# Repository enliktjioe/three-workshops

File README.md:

# three-workshops
HfK Bremen - Three Workshops course from Ralf Baecker

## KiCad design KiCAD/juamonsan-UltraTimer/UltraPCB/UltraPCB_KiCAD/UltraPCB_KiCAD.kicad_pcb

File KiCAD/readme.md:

# KiCAD Notes

## Day 3 - Designing, Simulating and Running Installation with [Processing.org](http://processing.org/)

## Day 2 - KiCAD PCB continuation

Using reference:
https://github.com/juamonsan/UltraTimer

A custom PCB board with a STM32 microcontroller, 7 seg display, a buzzer and many leds... In the shape of the #1 hero of all galaxy. Made with [KiCAD](https://www.kicad.org/), [Inkscape](https://inkscape.org/), [Gingerbread](https://github.com/wntrblm/Gingerbread) and [Stretch](https://github.com/JarrettR/Stretch). Programmed with [STM32CubeIDE](https://www.st.com/en/development-tools/stm32cubeide.html).

## Day 1 - KiCAD introduction

15.07.2025

Prof. Ralf Baecker

https://github.com/rlfbckr/workshops/tree/main

Presentation:
https://docs.google.com/presentation/d/1FQOJmnPphsIvtIlYlx94JYpmJ64v6YoRFoZGHLRAc9c/edit?slide=id.gb1fd486fc7_0_359#slide=id.gb1fd486fc7_0_359

Miro Canvas:
https://miro.com/app/board/uXjVJfeq8kw=/

Getting Started:
https://docs.kicad.org/6.0/en/getting_started_in_kicad/getting_started_in_kicad.html#basic_concepts_and_workflow

Example projects:

- https://www.martinhesselmeier.com/saroskop/
- https://gieskes.nl/

Other References:

- https://github.com/joanbono/awesome-kicad

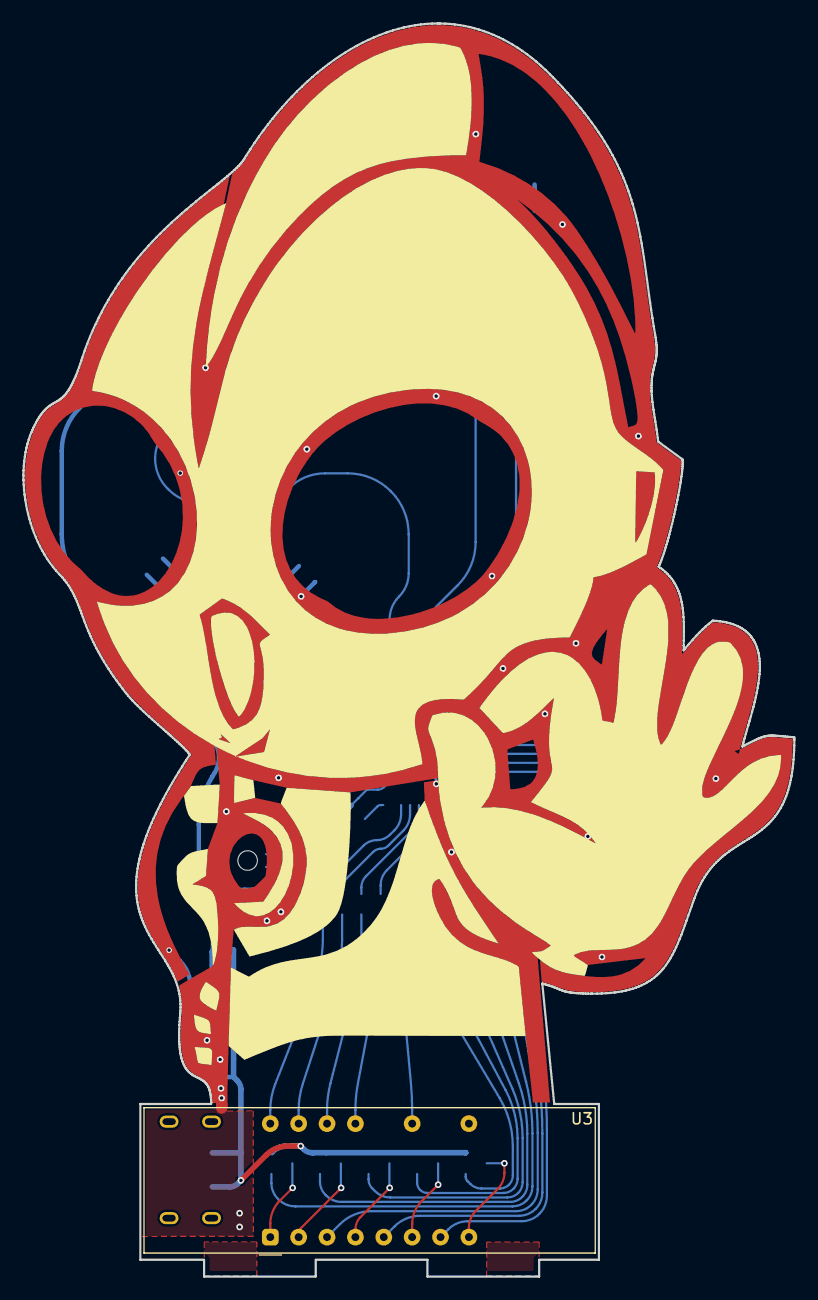
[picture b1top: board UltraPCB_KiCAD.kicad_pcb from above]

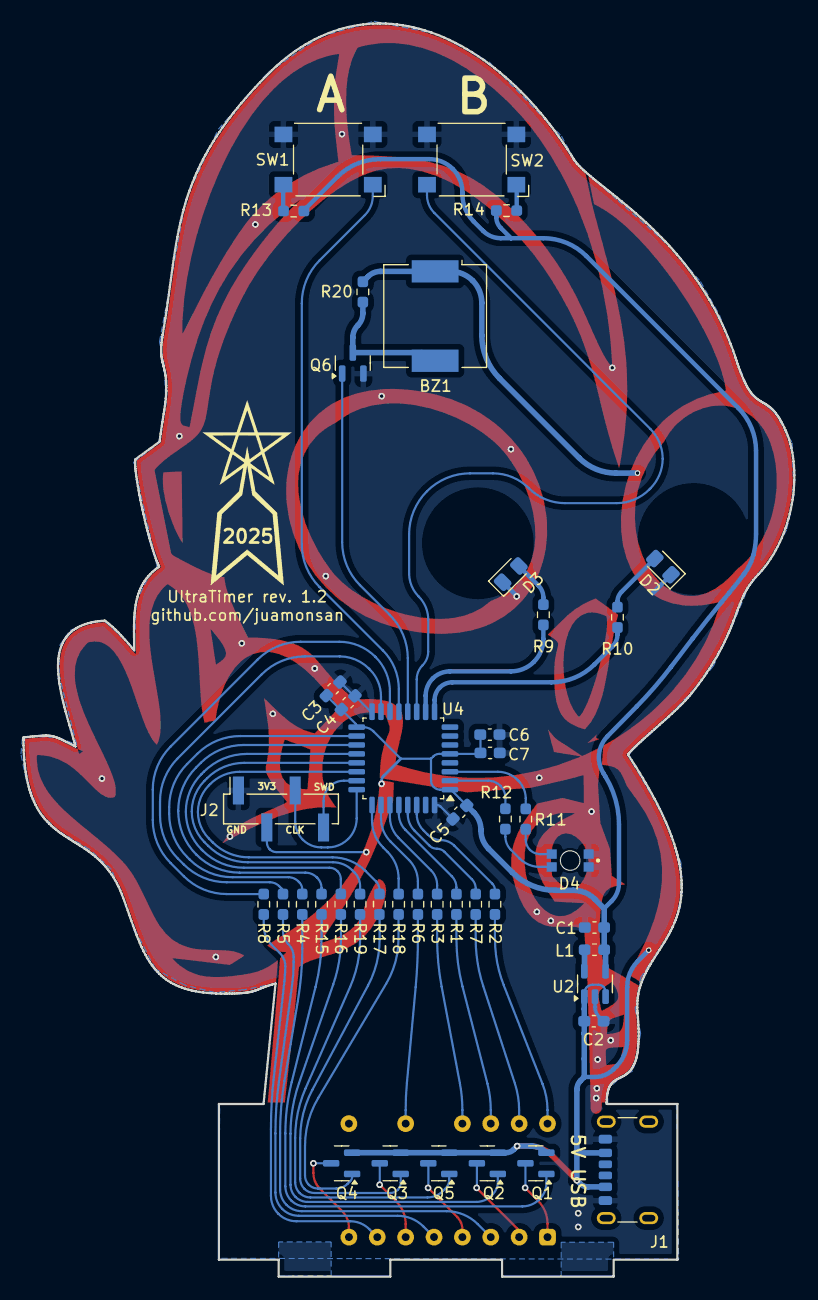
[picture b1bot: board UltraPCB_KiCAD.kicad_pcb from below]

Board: 2 copper layers, 69.0 x 112.2 mm, 45 parts (44 on the bottom side), 49 nets.

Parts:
BZ1: CPT-9019S-SMT-TR; Buzzer_CUI_CPT-9019S-SMT
C1: 10uF; C_0603_1608Metric_Pad1.08x0.95mm_HandSolder
C2, C3: 4.7uF; C_0603_1608Metric_Pad1.08x0.95mm_HandSolder
C4, C5: 100nF; C_0603_1608Metric_Pad1.08x0.95mm_HandSolder
C6: 10nF; C_0603_1608Metric_Pad1.08x0.95mm_HandSolder
C7: 1uF; C_0603_1608Metric_Pad1.08x0.95mm_HandSolder
D2, D3: LED; LED_0805_2012Metric_Pad1.15x1.40mm_HandSolder
D4: Red & Blue, 120°; WL-SBRW_1205_reverse mount
J1: USB_C_Receptacle_PowerOnly_6P; USB_C_Receptacle_GCT_USB4125-xx-x-0190_6P_TopMnt_Horizontal
J2: Conn_01x04_Pin; PinHeader_1x04_P2.54mm_Vertical_SMD_Pin1Right
L1: 10uH; L_0603_1608Metric_Pad1.05x0.95mm_HandSolder
Q1, Q2, Q3, Q4, Q5: SQ2325ES-T1_GE3; SOT-23
Q6: IRLML6244; SOT-23
R1, R2, R3, R4, R5, R6, R7, R8, R9, R10, R11, R12: 470; R_0603_1608Metric_Pad0.98x0.95mm_HandSolder
R13, R14, R20: 1k; R_0603_1608Metric_Pad0.98x0.95mm_HandSolder
R15, R16, R17, R18, R19: 10k; R_0603_1608Metric_Pad0.98x0.95mm_HandSolder
SW1, SW2: SW_Push; SW_SPST_Omron_B3FS-100xP
U2: LM3670MF-3.3; TSOT-23-5
U3: LTC-4627JD; LTC-4627Jx
U4: STM32F030K6Tx; LQFP-32_7x7mm_P0.8mm

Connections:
+3V3: C1.1, C3.1, C4.1, C5.1, C6.1, C7.1, J2.2, L1.2, R13.2, R14.2, U2.4 (FB), U4.1 (VDD), U4.5 (VDDA), U4.17 (VDD)
+5V: BZ1.1 (+), C2.1, J1.A9 (VBUS), J1.B9 (VBUS), Q1.2 (S), Q2.2 (S), Q3.2 (S), Q4.2 (S), Q5.2 (S), R20.2, U2.1 (Vin), U2.3 (EN)
/CA1: Q1.3 (D), U3.1 (CA1)
/CA2: Q2.3 (D), U3.2 (CA2)
/CA3: Q3.3 (D), U3.6 (CA3)
/CA4: Q4.3 (D), U3.8 (CA4)
/CAL: Q5.3 (D), U3.4 (CAL)
/DispA: R1.1, U4.28 (PB5)
/DispB: R2.1, U4.30 (PB7)
/DispC: R3.1, U4.27 (PB4)
/DispD: R4.1, U4.18 (PA8)
/DispDP: R8.1, U4.14 (PB0)
/DispE: R5.1, U4.15 (PB1)
/DispF: R6.1, U4.26 (PB3)
/DispG: R7.1, U4.29 (PB6)
/Display1: R15.2, U4.19 (PA9)
/Display2: R16.2, U4.20 (PA10)
/Display3: R17.2, U4.22 (PA12)
/Display4: R18.2, U4.25 (PA15)
/DisplayL: R19.2, U4.21 (PA11)
/LED1: R10.2, U4.9 (PA3)
/LED2: R9.2, U4.10 (PA4)
/LED_Blue: R12.1, U4.2 (PF0)
/LED_Red: R11.1, U4.3 (PF1)
/SW1_IN: R13.1, SW1.1, U4.13 (PA7)
/SW2_IN: R14.1, SW2.1, U4.11 (PA5)
/SWCLK: J2.3, U4.24 (PA14)
/SWDIO: J2.4, U4.23 (PA13)
/Timer3_PWM: Q6.1 (G), U4.12 (PA6)
GND: C1.2, C2.2, C3.2, C4.2, C5.2, C6.2, C7.2, D2.1 (K), D3.1 (K), D4.1 (K), D4.2 (K), J1.A12 (GND), J1.B12 (GND), J2.1, Q6.2 (S), SW1.2, SW2.2, U2.2 (GND), U4.16 (VSS), U4.32 (VSS)
unnamed: BZ1.2 (-), Q6.3 (D), R20.1
unnamed: D2.2 (A), R10.1
unnamed: D3.2 (A), R9.1
unnamed: D4.3 (A), R11.2
unnamed: D4.4 (A), R12.2
unnamed: Q1.1 (G), R15.1
unnamed: Q2.1 (G), R16.1
unnamed: Q3.1 (G), R17.1
unnamed: Q4.1 (G), R18.1
unnamed: Q5.1 (G), R19.1
unnamed: L1.1, U2.5 (SW)
unnamed: R1.2, U3.14 (A)
unnamed: R2.2, U3.16 (B)
unnamed: R3.2, U3.13 (C)
unnamed: R4.2, U3.3 (D)
unnamed: R8.2, U3.7 (DP)
unnamed: R5.2, U3.5 (E)
unnamed: R6.2, U3.11 (F)
unnamed: R7.2, U3.15 (G)

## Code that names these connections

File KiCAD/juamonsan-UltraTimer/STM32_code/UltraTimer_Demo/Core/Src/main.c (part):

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  int Ref_time=2;

  /* Blue Start */
  HAL_GPIO_TogglePin(LED_Red_GPIO_Port, LED_Red_Pin);
  /* Eyes on*/
  HAL_GPIO_TogglePin(LED1_GPIO_Port, LED1_Pin);
  HAL_GPIO_TogglePin(LED2_GPIO_Port, LED2_Pin);

  /* Display OFF */
  DisplayNumber(0,10);
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
	  }

//	  HAL_GPIO_TogglePin(LED_Blue_GPIO_Port, LED_Blue_Pin);
//	  HAL_GPIO_TogglePin(LED_Red_GPIO_Port, LED_Red_Pin);
//	  __HAL_TIM_SET_PRESCALER(&htim3, presForFrequency(900));
//	  HAL_Delay(150);
//	  __HAL_TIM_SET_PRESCALER(&htim3, presForFrequency(500));
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  __HAL_RCC_GPIOB_CLK_ENABLE();

  /*Configure GPIO pin Output Level */
  HAL_GPIO_WritePin(GPIOF, LED_Blue_Pin|LED_Red_Pin, GPIO_PIN_RESET);

  /*Configure GPIO pin Output Level */
  HAL_GPIO_WritePin(GPIOA, LED1_Pin|LED2_Pin|DispD_Pin|Display1_Pin
                          |Display2_Pin|DisplayL_Pin|Display3_Pin|Display4_Pin, GPIO_PIN_RESET);

  /*Configure GPIO pin Output Level */
  HAL_GPIO_WritePin(GPIOB, DispDP_Pin|DispE_Pin|DispF_Pin|DispC_Pin
                          |DispA_Pin|DispG_Pin|DispB_Pin, GPIO_PIN_RESET);

  /*Configure GPIO pins : LED_Blue_Pin LED_Red_Pin */
  GPIO_InitStruct.Pin = LED_Blue_Pin|LED_Red_Pin;
  GPIO_InitStruct.Mode = GPIO_MODE_OUTPUT_PP;
  GPIO_InitStruct.Pull = GPIO_NOPULL;
  GPIO_InitStruct.Speed = GPIO_SPEED_FREQ_LOW;
  HAL_GPIO_Init(GPIOF, &GPIO_InitStruct);

  /*Configure GPIO pins : LED1_Pin LED2_Pin DispD_Pin Display1_Pin
                           Display2_Pin DisplayL_Pin Display3_Pin Display4_Pin */
  GPIO_InitStruct.Pin = LED1_Pin|LED2_Pin|DispD_Pin|Display1_Pin
                          |Display2_Pin|DisplayL_Pin|Display3_Pin|Display4_Pin;
  GPIO_InitStruct.Mode = GPIO_MODE_OUTPUT_PP;
  GPIO_InitStruct.Pull = GPIO_NOPULL;
  GPIO_InitStruct.Speed = GPIO_SPEED_FREQ_LOW;
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  GPIO_InitStruct.Pull = GPIO_PULLDOWN;
  HAL_GPIO_Init(GPIOA, &GPIO_InitStruct);

  /*Configure GPIO pins : DispDP_Pin DispE_Pin DispF_Pin DispC_Pin
                           DispA_Pin DispG_Pin DispB_Pin */
  GPIO_InitStruct.Pin = DispDP_Pin|DispE_Pin|DispF_Pin|DispC_Pin
                          |DispA_Pin|DispG_Pin|DispB_Pin;
  GPIO_InitStruct.Mode = GPIO_MODE_OUTPUT_PP;
  GPIO_InitStruct.Pull = GPIO_NOPULL;
  GPIO_InitStruct.Speed = GPIO_SPEED_FREQ_LOW;
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{

	if(HAL_GPIO_ReadPin(B_Button_EXTI_GPIO_Port, B_Button_EXTI_Pin) == GPIO_PIN_RESET){
		HAL_GPIO_TogglePin(LED_Blue_GPIO_Port, LED_Red_Pin);
		HAL_GPIO_TogglePin(LED_Blue_GPIO_Port, LED_Blue_Pin);
		state = true;
		HAL_TIM_Base_Stop_IT(&htim1);
	}
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void DisplayNumber(uint8_t Position, uint8_t Number){
	switch (Position){
		case 1:
			HAL_GPIO_WritePin(Display1_GPIO_Port, Display1_Pin, GPIO_PIN_RESET);
			HAL_GPIO_WritePin(Display2_GPIO_Port, Display2_Pin, GPIO_PIN_SET);
			HAL_GPIO_WritePin(Display3_GPIO_Port, Display3_Pin, GPIO_PIN_SET);
			HAL_GPIO_WritePin(Display4_GPIO_Port, Display4_Pin, GPIO_PIN_SET);
			HAL_GPIO_WritePin(DisplayL_GPIO_Port, DisplayL_Pin, GPIO_PIN_SET);
			break;
		case 2:
			HAL_GPIO_WritePin(Display1_GPIO_Port, Display1_Pin, GPIO_PIN_SET);
			HAL_GPIO_WritePin(Display2_GPIO_Port, Display2_Pin, GPIO_PIN_RESET);
			HAL_GPIO_WritePin(Display3_GPIO_Port, Display3_Pin, GPIO_PIN_SET);
			HAL_GPIO_WritePin(Display4_GPIO_Port, Display4_Pin, GPIO_PIN_SET);
			HAL_GPIO_WritePin(DisplayL_GPIO_Port, DisplayL_Pin, GPIO_PIN_SET);
			break;
		case 3:
			HAL_GPIO_WritePin(Display1_GPIO_Port, Display1_Pin, GPIO_PIN_SET);
			HAL_GPIO_WritePin(Display2_GPIO_Port, Display2_Pin, GPIO_PIN_SET);
			HAL_GPIO_WritePin(Display3_GPIO_Port, Display3_Pin, GPIO_PIN_RESET);
			HAL_GPIO_WritePin(Display4_GPIO_Port, Display4_Pin, GPIO_PIN_SET);
			HAL_GPIO_WritePin(DisplayL_GPIO_Port, DisplayL_Pin, GPIO_PIN_SET);
			break;
		case 4:
			HAL_GPIO_WritePin(Display1_GPIO_Port, Display1_Pin, GPIO_PIN_SET);
			HAL_GPIO_WritePin(Display2_GPIO_Port, Display2_Pin, GPIO_PIN_SET);
			HAL_GPIO_WritePin(Display3_GPIO_Port, Display3_Pin, GPIO_PIN_SET);
			HAL_GPIO_WritePin(Display4_GPIO_Port, Display4_Pin, GPIO_PIN_RESET);
			HAL_GPIO_WritePin(DisplayL_GPIO_Port, DisplayL_Pin, GPIO_PIN_SET);
			break;
		case 5:
			HAL_GPIO_WritePin(Display1_GPIO_Port, Display1_Pin, GPIO_PIN_SET);
			HAL_GPIO_WritePin(Display2_GPIO_Port, Display2_Pin, GPIO_PIN_SET);
			HAL_GPIO_WritePin(Display3_GPIO_Port, Display3_Pin, GPIO_PIN_SET);
			HAL_GPIO_WritePin(Display4_GPIO_Port, Display4_Pin, GPIO_PIN_SET);
			HAL_GPIO_WritePin(DisplayL_GPIO_Port, DisplayL_Pin, GPIO_PIN_RESET);
			break;
		case 0:
			//all off
			HAL_GPIO_WritePin(Display1_GPIO_Port, Display1_Pin, GPIO_PIN_SET);
			HAL_GPIO_WritePin(Display2_GPIO_Port, Display2_Pin, GPIO_PIN_SET);
			HAL_GPIO_WritePin(Display3_GPIO_Port, Display3_Pin, GPIO_PIN_SET);
			HAL_GPIO_WritePin(Display4_GPIO_Port, Display4_Pin, GPIO_PIN_SET);
			HAL_GPIO_WritePin(DisplayL_GPIO_Port, DisplayL_Pin, GPIO_PIN_SET);
			break;

	}
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		//case 0:

		case 1:
			HAL_GPIO_WritePin(DispA_GPIO_Port, DispA_Pin, GPIO_PIN_SET);
			HAL_GPIO_WritePin(DispB_GPIO_Port, DispB_Pin, GPIO_PIN_RESET);
			HAL_GPIO_WritePin(DispC_GPIO_Port, DispC_Pin, GPIO_PIN_RESET);
			HAL_GPIO_WritePin(DispD_GPIO_Port, DispD_Pin, GPIO_PIN_SET);
			HAL_GPIO_WritePin(DispE_GPIO_Port, DispE_Pin, GPIO_PIN_SET);
			HAL_GPIO_WritePin(DispF_GPIO_Port, DispF_Pin, GPIO_PIN_SET);
			HAL_GPIO_WritePin(DispG_GPIO_Port, DispG_Pin, GPIO_PIN_SET);
			HAL_GPIO_WritePin(DispDP_GPIO_Port, DispDP_Pin, GPIO_PIN_SET);
			break;
		case 2:
			HAL_GPIO_WritePin(DispA_GPIO_Port, DispA_Pin, GPIO_PIN_RESET);
			HAL_GPIO_WritePin(DispB_GPIO_Port, DispB_Pin, GPIO_PIN_RESET);
			HAL_GPIO_WritePin(DispC_GPIO_Port, DispC_Pin, GPIO_PIN_SET);
			HAL_GPIO_WritePin(DispD_GPIO_Port, DispD_Pin, GPIO_PIN_RESET);
			HAL_GPIO_WritePin(DispE_GPIO_Port, DispE_Pin, GPIO_PIN_RESET);
			HAL_GPIO_WritePin(DispF_GPIO_Port, DispF_Pin, GPIO_PIN_SET);
			HAL_GPIO_WritePin(DispG_GPIO_Port, DispG_Pin, GPIO_PIN_RESET);
			HAL_GPIO_WritePin(DispDP_GPIO_Port, DispDP_Pin, GPIO_PIN_SET);
			break;
		case 3:
			HAL_GPIO_WritePin(DispA_GPIO_Port, DispA_Pin, GPIO_PIN_RESET);
			HAL_GPIO_WritePin(DispB_GPIO_Port, DispB_Pin, GPIO_PIN_RESET);
			HAL_GPIO_WritePin(DispC_GPIO_Port, DispC_Pin, GPIO_PIN_RESET);
			HAL_GPIO_WritePin(DispD_GPIO_Port, DispD_Pin, GPIO_PIN_RESET);
			HAL_GPIO_WritePin(DispE_GPIO_Port, DispE_Pin, GPIO_PIN_SET);
			HAL_GPIO_WritePin(DispF_GPIO_Port, DispF_Pin, GPIO_PIN_SET);
			HAL_GPIO_WritePin(DispG_GPIO_Port, DispG_Pin, GPIO_PIN_RESET);
			HAL_GPIO_WritePin(DispDP_GPIO_Port, DispDP_Pin, GPIO_PIN_SET);
			break;
		case 4:
			HAL_GPIO_WritePin(DispA_GPIO_Port, DispA_Pin, GPIO_PIN_SET);
			HAL_GPIO_WritePin(DispB_GPIO_Port, DispB_Pin, GPIO_PIN_RESET);
			HAL_GPIO_WritePin(DispC_GPIO_Port, DispC_Pin, GPIO_PIN_RESET);
			HAL_GPIO_WritePin(DispD_GPIO_Port, DispD_Pin, GPIO_PIN_SET);
			HAL_GPIO_WritePin(DispE_GPIO_Port, DispE_Pin, GPIO_PIN_SET);
			HAL_GPIO_WritePin(DispF_GPIO_Port, DispF_Pin, GPIO_PIN_RESET);
			HAL_GPIO_WritePin(DispG_GPIO_Port, DispG_Pin, GPIO_PIN_RESET);
			HAL_GPIO_WritePin(DispDP_GPIO_Port, DispDP_Pin, GPIO_PIN_SET);
			break;
		case 10:
			//all off
			HAL_GPIO_WritePin(DispA_GPIO_Port, DispA_Pin, GPIO_PIN_SET);
			HAL_GPIO_WritePin(DispB_GPIO_Port, DispB_Pin, GPIO_PIN_SET);
			HAL_GPIO_WritePin(DispC_GPIO_Port, DispC_Pin, GPIO_PIN_SET);
			HAL_GPIO_WritePin(DispD_GPIO_Port, DispD_Pin, GPIO_PIN_SET);
			HAL_GPIO_WritePin(DispE_GPIO_Port, DispE_Pin, GPIO_PIN_SET);
			HAL_GPIO_WritePin(DispF_GPIO_Port, DispF_Pin, GPIO_PIN_SET);
			HAL_GPIO_WritePin(DispG_GPIO_Port, DispG_Pin, GPIO_PIN_SET);
			HAL_GPIO_WritePin(DispDP_GPIO_Port, DispDP_Pin, GPIO_PIN_SET);
			break;
	}

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
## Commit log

2025-05-19 intro session 19.05.2025
2025-05-20 second session 20.05.2025 - multiple fungis
2025-07-15 starting point - KiCAD workshop
2025-07-16 finished for today
2025-07-16 added new reference
2025-07-16 finished 2nd day
2025-07-17 added Prof. Ralf pcb project
2025-07-17 minor
2025-07-17 day 3 - arduino

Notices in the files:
KiCAD/juamonsan-UltraTimer/STM32_code/UltraTimer_Demo/Core/Src/main.c:
Copyright (c) 2024 STMicroelectronics.
All rights reserved.
This software is licensed under terms that can be found in the LICENSE file
